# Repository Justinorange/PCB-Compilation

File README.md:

# PCB-Compilation

A collection of custom PCB designs, prototypes, and lab projects built for research and experimentation.

## [Relay Control Board](https://github.com/uf-mil-electrical/NaviGator/tree/3adb6dfac39e3fa88b3697202d415e38e3245c48/Kill%20Board/2026/Relay-Board-PCB/Relay-Board)

A robust relay control and safety management board designed for hardware kill switching, power distribution, and status monitoring.

### Key Features:
- **Relay Outputs:** Features 7 relay outputs with selectable 12V and MCU-level voltage control options, protected by a fuse and TVS diode.
- **Kill & Safety System:** 
  * 6 input signals with individual red status LEDs to monitor when a kill state is active.
  * 2 dedicated inputs for manual override (enables the yellow status indicator; overridden by the red kill state).
  * Active high/low configuration jumpers for flexible input/output logic.
  * Hardware override jumper to unkill the system.
- **Light Tower Status Indicators:** Built using 0803 SMD LEDs for clean labeling and visual feedback:
  * **Enable**
  * **Red:** Kill enabled
  * **Yellow:** Manual enable
  * **Green:** Autonomous / default operation

View the project source and design files on [GitHub](https://github.com/uf-mil-electrical/NaviGator/tree/3adb6dfac39e3fa88b3697202d415e38e3245c48/Kill%20Board/2026/Relay-Board-PCB/Relay-Board).

## [Air Quality Sensor Breakout Boards](https://github.com/uf-mil-electrical/misc_hardware/tree/7a44acb8b002e7d45b233cf23141b061ac4c3471/Sensing/Sensor_Breakouts)

I am building a set of sensor breakout boards that will eventually be combined into a single air quality sensing PCB. These boards are still in progress, and I am finishing the analog sensor boards before moving on to the digital ones.

These breakout boards were made for the Machine Intelligence Laboratory (MIL) and are part of a larger integrated sensing platform. View the breakout designs on [GitHub](https://github.com/uf-mil-electrical/misc_hardware/tree/7a44acb8b002e7d45b233cf23141b061ac4c3471/Sensing/Sensor_Breakouts).

## [STUSB 4500 Controller](https://github.com/Justinorange/STUSB4500-Arduino-Controller)

The STUSB 4500 controller is one of the more complicated PCBs I have made, largely due to the use of USB C protocols and having to solder it by hand.

This board was made for FOCUS Lab last year and represents a more complex design in the collection. View the project source on [GitHub](https://github.com/Justinorange/STUSB4500-Arduino-Controller).

## [Flashlight Project](https://github.com/Justinorange/Flashlight)

This was a quick and fun project to build two flashlights that produce over 20,000 lumens each while keeping the cost as low as possible. The total cost for both was approximately $50. (I also just wanted to make a single sided aluminum PCB).

View the repository and design files on [GitHub](https://github.com/Justinorange/Flashlight).

## Project Summary

This repository highlights a diverse range of custom PCB projects, including modular air quality and hydrogen sensor systems, a comprehensive relay control board with hardware safety features, research-focused USB-C power controllers, and high-output lighting builds.

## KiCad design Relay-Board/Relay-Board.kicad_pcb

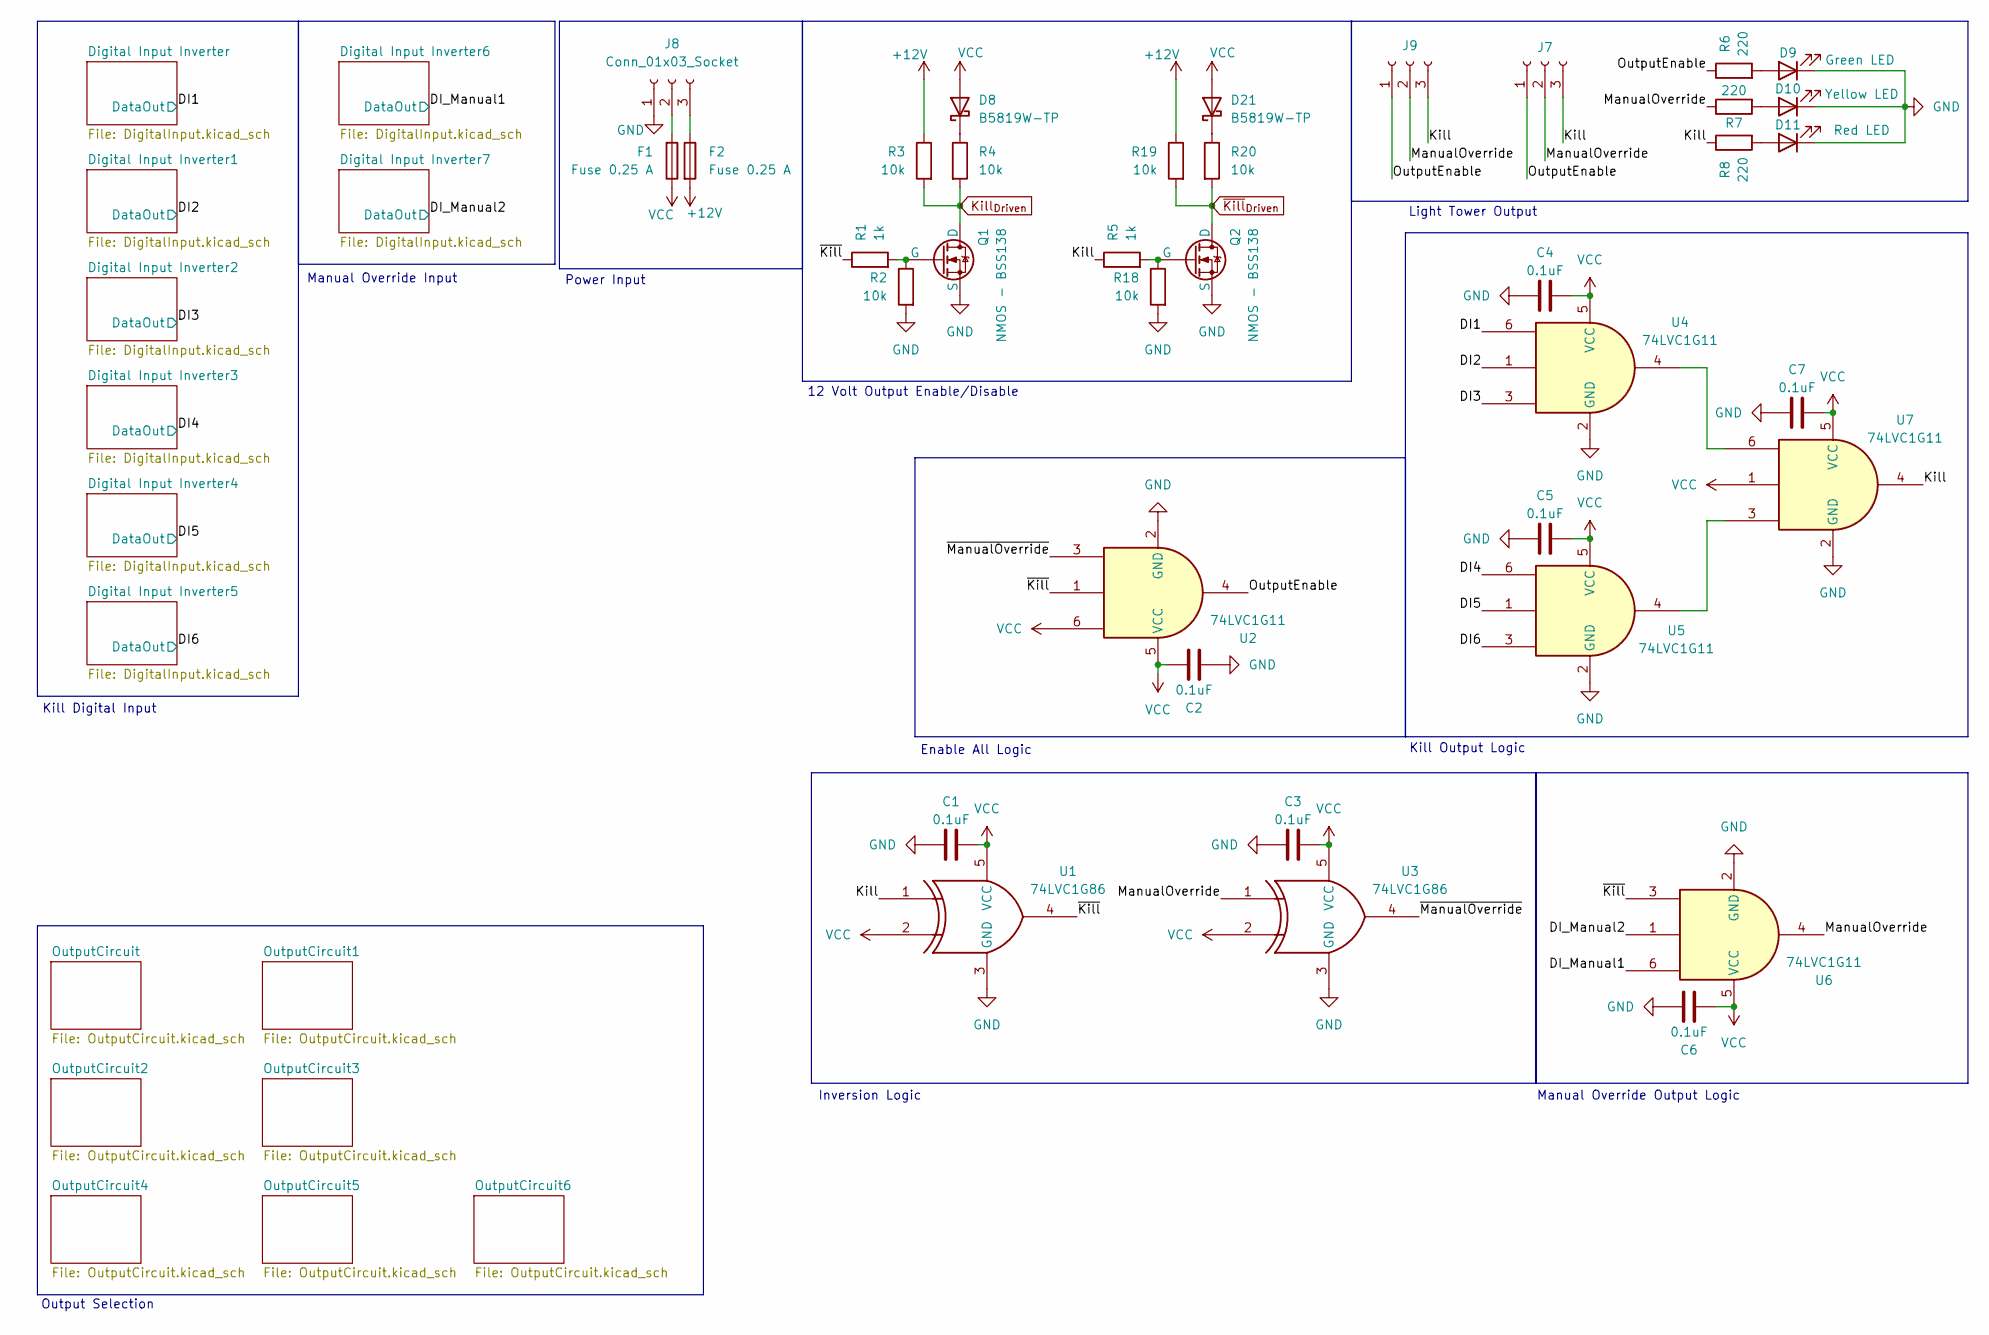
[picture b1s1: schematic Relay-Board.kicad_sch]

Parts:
C1, C2, C3, C4, C5, C6, C7: 0.1uF; C_0603_1608Metric_Pad1.08x0.95mm_HandSolder
D8, D21: B5819W-TP; D_SOD-123
D9: Green LED; LED_0805_2012Metric_Pad1.15x1.40mm_HandSolder
D10: Yellow LED; LED_0805_2012Metric_Pad1.15x1.40mm_HandSolder
D11: Red LED; LED_0805_2012Metric_Pad1.15x1.40mm_HandSolder
F1, F2: Fuse 0.25 A; Fuse_1206_3216Metric_Pad1.42x1.75mm_HandSolder
J7, J8, J9: Conn_01x03_Socket; Molex_Micro-Latch_53253-0370_1x03_P2.00mm_Vertical
Q1, Q2: NMOS - BSS138; SC-59_Handsoldering
R1, R5: 1k; R_0603_1608Metric_Pad0.98x0.95mm_HandSolder
R2, R3, R4, R18, R19, R20: 10k; R_0603_1608Metric_Pad0.98x0.95mm_HandSolder
R6, R7, R8: 220; R_0603_1608Metric_Pad0.98x0.95mm_HandSolder
U1, U3: 74LVC1G86; Texas_R-PDSO-G5_DCK-5
U2, U4, U5, U6, U7: 74LVC1G11; SOT-23-6_Handsoldering

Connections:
+12V: F2.2, R3.1, R19.1; also elsewhere on the board
/DI1: U4.6; also elsewhere on the board
/DI2: U4.1; also elsewhere on the board
/DI3: U4.3; also elsewhere on the board
/DI4: U5.6; also elsewhere on the board
/DI5: U5.1; also elsewhere on the board
/DI6: U5.3; also elsewhere on the board
/DI_Manual1: U6.6; also elsewhere on the board
/DI_Manual2: U6.1; also elsewhere on the board
/Kill: J7.3, J9.3, R5.1, R8.1, U1.1, U7.4
/ManualOverride: J7.2, J9.2, R7.1, U3.1, U6.4
/OutputEnable: J7.1, J9.1, R6.1, U2.4
/~Kill: R1.1, U1.4, U2.1, U6.3
/~ManualOverride: U2.3, U3.4
GND: C1.2, C2.2, C3.2, C4.2, C5.2, C6.2, C7.2, D9.1 (K), D10.1 (K), D11.1 (K), J8.1, Q1.3 (S), Q2.3 (S), R2.2, R18.2, U1.3 (GND), U2.2 (GND), U3.3 (GND), U4.2 (GND), U5.2 (GND), U6.2 (GND), U7.2 (GND); also elsewhere on the board
Kill_{Driven}: Q1.1 (D), R3.2, R4.2; also elsewhere on the board
unnamed: D8.1 (K), R4.1
unnamed: D9.2 (A), R6.2
unnamed: D10.2 (A), R7.2
unnamed: D11.2 (A), R8.2
unnamed: D21.1 (K), R20.1
unnamed: F1.2, J8.2
unnamed: F2.1, J8.3
unnamed: Q1.2 (G), R1.2, R2.1
unnamed: Q2.2 (G), R5.2, R18.1
unnamed: U4.4, U7.6
unnamed: U5.4, U7.3
VCC: C1.1, C2.1, C3.1, C4.1, C5.1, C6.1, C7.1, D8.2 (A), D21.2 (A), F1.1, U1.2, U1.5 (VCC), U2.5 (VCC), U2.6, U3.2, U3.5 (VCC), U4.5 (VCC), U5.5 (VCC), U6.5 (VCC), U7.1, U7.5 (VCC); also elsewhere on the board
~Kill_{Driven}: Q2.1 (D), R19.2, R20.2; also elsewhere on the board

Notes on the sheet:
Kill Digital Input
Output Selection
Power Input
Inversion Logic
Kill Output Logic
Enable All Logic
Manual Override Output Logic
Manual Override Input
Light Tower Output
12 Volt Output Enable/Disable

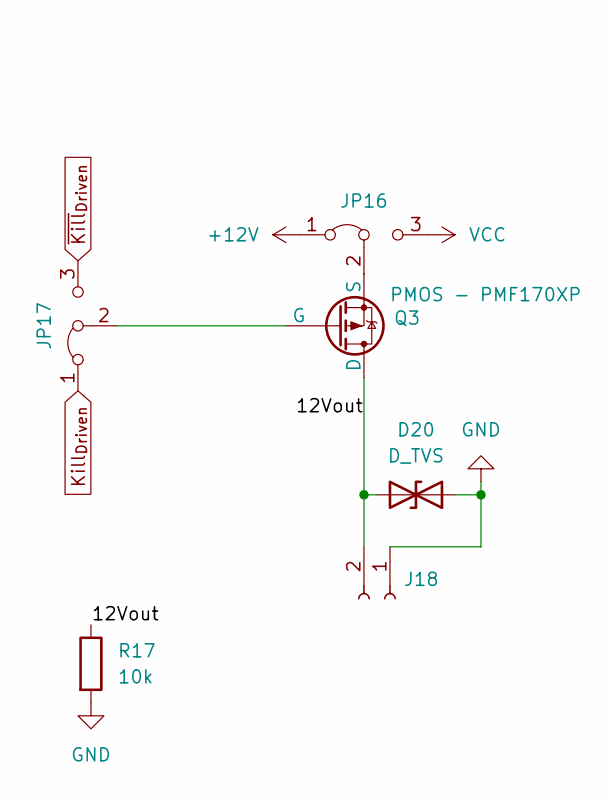
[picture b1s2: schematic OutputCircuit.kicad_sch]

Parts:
D20: D_TVS; D_SMB
J18: Conn_01x02_Socket; Molex_Micro-Latch_53253-0270_1x02_P2.00mm_Vertical
JP16, JP17: Jumper_3_Bridged12; PinHeader_1x03_P2.54mm_Vertical
Q3: PMOS - PMF170XP; SOT-323_SC-70_Handsoldering
R17: 10k; R_0603_1608Metric_Pad0.98x0.95mm_HandSolder

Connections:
+12V: JP16.1 (A); also elsewhere on the board
/OutputCircuit/12Vout: D20.2 (A2), J18.2, Q3.1 (D), R17.1
GND: D20.1 (A1), J18.1, R17.2; also elsewhere on the board
Kill_{Driven}: JP17.1 (A); also elsewhere on the board
unnamed: JP16.2 (C), Q3.3 (S)
unnamed: JP17.2 (C), Q3.2 (G)
VCC: JP16.3 (B); also elsewhere on the board
~Kill_{Driven}: JP17.3 (B); also elsewhere on the board

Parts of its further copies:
D1, D2, D3, D4, D5, D6: D_TVS; D_SMB
J1, J2, J3, J4, J5, J6: Conn_01x02_Socket; Molex_Micro-Latch_53253-0270_1x02_P2.00mm_Vertical
JP1, JP2, JP3, JP4, JP5, JP6, JP7, JP18, JP19, JP20, JP21, JP22: Jumper_3_Bridged12; PinHeader_1x03_P2.54mm_Vertical
Q4, Q5, Q6, Q7, Q8, Q9: PMOS - PMF170XP; SOT-323_SC-70_Handsoldering
R21, R22, R23, R24, R25, R26: 10k; R_0603_1608Metric_Pad0.98x0.95mm_HandSolder

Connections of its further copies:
+12V: JP3.1 (A), JP4.1 (A), JP6.1 (A), JP18.1 (A), JP20.1 (A), JP22.1 (A); also elsewhere on the board
/OutputCircuit1/12Vout: D1.2 (A2), J1.2, Q4.1 (D), R21.1
/OutputCircuit2/12Vout: D2.2 (A2), J2.2, Q5.1 (D), R22.1
/OutputCircuit3/12Vout: D3.2 (A2), J3.2, Q6.1 (D), R23.1
/OutputCircuit4/12Vout: D4.2 (A2), J4.2, Q7.1 (D), R24.1
/OutputCircuit5/12Vout: D5.2 (A2), J5.2, Q8.1 (D), R25.1
/OutputCircuit6/12Vout: D6.2 (A2), J6.2, Q9.1 (D), R26.1
GND: D1.1 (A1), D2.1 (A1), D3.1 (A1), D4.1 (A1), D5.1 (A1), D6.1 (A1), J1.1, J2.1, J3.1, J4.1, J5.1, J6.1, R21.2, R22.2, R23.2, R24.2, R25.2, R26.2; also elsewhere on the board
Kill_{Driven}: JP1.1 (A), JP2.1 (A), JP5.1 (A), JP7.1 (A), JP19.1 (A), JP21.1 (A); also elsewhere on the board
unnamed: JP1.2 (C), Q4.2 (G)
unnamed: JP2.2 (C), Q5.2 (G)
unnamed: JP3.2 (C), Q5.3 (S)
unnamed: JP4.2 (C), Q4.3 (S)
unnamed: JP5.2 (C), Q6.2 (G)
unnamed: JP6.2 (C), Q6.3 (S)
unnamed: JP7.2 (C), Q7.2 (G)
unnamed: JP18.2 (C), Q7.3 (S)
unnamed: JP19.2 (C), Q8.2 (G)
unnamed: JP20.2 (C), Q8.3 (S)
unnamed: JP21.2 (C), Q9.2 (G)
unnamed: JP22.2 (C), Q9.3 (S)
VCC: JP3.3 (B), JP4.3 (B), JP6.3 (B), JP18.3 (B), JP20.3 (B), JP22.3 (B); also elsewhere on the board
~Kill_{Driven}: JP1.3 (B), JP2.3 (B), JP5.3 (B), JP7.3 (B), JP19.3 (B), JP21.3 (B); also elsewhere on the board

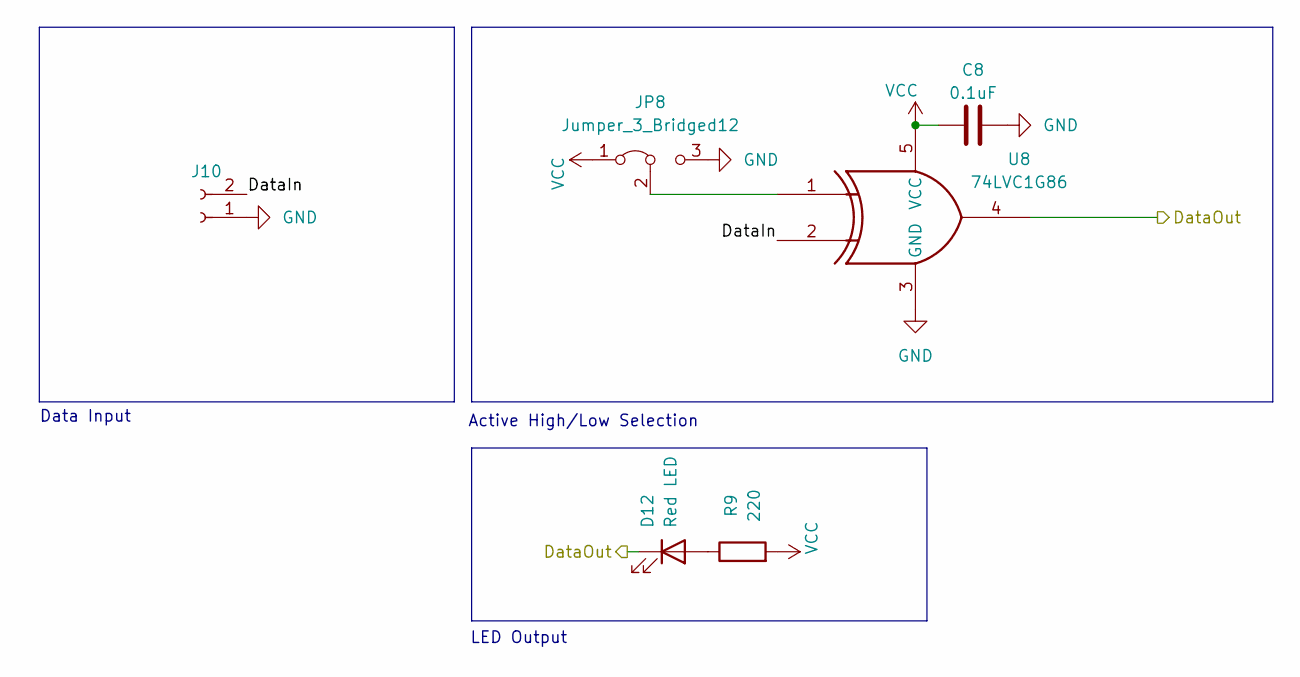
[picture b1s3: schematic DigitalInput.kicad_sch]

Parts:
C8: 0.1uF; C_0603_1608Metric_Pad1.08x0.95mm_HandSolder
D12: Red LED; LED_0805_2012Metric_Pad1.15x1.40mm_HandSolder
J10: Conn_01x02_Socket; Molex_Micro-Latch_53253-0270_1x02_P2.00mm_Vertical
JP8: Jumper_3_Bridged12; PinHeader_1x03_P2.54mm_Vertical
R9: 220; R_0603_1608Metric_Pad0.98x0.95mm_HandSolder
U8: 74LVC1G86; Texas_R-PDSO-G5_DCK-5

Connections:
/DI1: D12.1 (K), U8.4; also elsewhere on the board
/Digital Input Inverter/DataIn: J10.2, U8.2
GND: C8.2, J10.1, JP8.3 (B), U8.3 (GND); also elsewhere on the board
unnamed: D12.2 (A), R9.1
unnamed: JP8.2 (C), U8.1
VCC: C8.1, JP8.1 (A), R9.2, U8.5 (VCC); also elsewhere on the board

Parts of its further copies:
C9, C10, C11, C12, C13, C14, C15: 0.1uF; C_0603_1608Metric_Pad1.08x0.95mm_HandSolder
D13, D14, D15, D16, D17, D18, D19: Red LED; LED_0805_2012Metric_Pad1.15x1.40mm_HandSolder
J11, J12, J13, J14, J15, J16, J17: Conn_01x02_Socket; Molex_Micro-Latch_53253-0270_1x02_P2.00mm_Vertical
JP9, JP10, JP11, JP12, JP13, JP14, JP15: Jumper_3_Bridged12; PinHeader_1x03_P2.54mm_Vertical
R10, R11, R12, R13, R14, R15, R16: 220; R_0603_1608Metric_Pad0.98x0.95mm_HandSolder
U9, U10, U11, U12, U13, U14, U15: 74LVC1G86; Texas_R-PDSO-G5_DCK-5

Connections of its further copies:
/DI2: D13.1 (K), U9.4; also elsewhere on the board
/DI3: D14.1 (K), U10.4; also elsewhere on the board
/DI4: D15.1 (K), U11.4; also elsewhere on the board
/DI5: D16.1 (K), U12.4; also elsewhere on the board
/DI6: D17.1 (K), U13.4; also elsewhere on the board
/DI_Manual1: D18.1 (K), U14.4; also elsewhere on the board
/DI_Manual2: D19.1 (K), U15.4; also elsewhere on the board
/Digital Input Inverter1/DataIn: J11.2, U9.2
/Digital Input Inverter2/DataIn: J12.2, U10.2
/Digital Input Inverter3/DataIn: J13.2, U11.2
/Digital Input Inverter4/DataIn: J14.2, U12.2
/Digital Input Inverter5/DataIn: J15.2, U13.2
/Digital Input Inverter6/DataIn: J16.2, U14.2
/Digital Input Inverter7/DataIn: J17.2, U15.2
GND: C9.2, C10.2, C11.2, C12.2, C13.2, C14.2, C15.2, J11.1, J12.1, J13.1, J14.1, J15.1, J16.1, J17.1, JP9.3 (B), JP10.3 (B), JP11.3 (B), JP12.3 (B), JP13.3 (B), JP14.3 (B), JP15.3 (B), U9.3 (GND), U10.3 (GND), U11.3 (GND), U12.3 (GND), U13.3 (GND), U14.3 (GND), U15.3 (GND); also elsewhere on the board
unnamed: D13.2 (A), R10.1
unnamed: D14.2 (A), R11.1
unnamed: D15.2 (A), R12.1
unnamed: D16.2 (A), R13.1
unnamed: D17.2 (A), R14.1
unnamed: D18.2 (A), R15.1
unnamed: D19.2 (A), R16.1
unnamed: JP9.2 (C), U9.1
unnamed: JP10.2 (C), U10.1
unnamed: JP11.2 (C), U11.1
unnamed: JP12.2 (C), U12.1
unnamed: JP13.2 (C), U13.1
unnamed: JP14.2 (C), U14.1
unnamed: JP15.2 (C), U15.1
VCC: C9.1, C10.1, C11.1, C12.1, C13.1, C14.1, C15.1, JP9.1 (A), JP10.1 (A), JP11.1 (A), JP12.1 (A), JP13.1 (A), JP14.1 (A), JP15.1 (A), R10.2, R11.2, R12.2, R13.2, R14.2, R15.2, R16.2, U9.5 (VCC), U10.5 (VCC), U11.5 (VCC), U12.5 (VCC), U13.5 (VCC), U14.5 (VCC), U15.5 (VCC); also elsewhere on the board

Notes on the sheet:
Active High/Low Selection
LED Output
Data Input

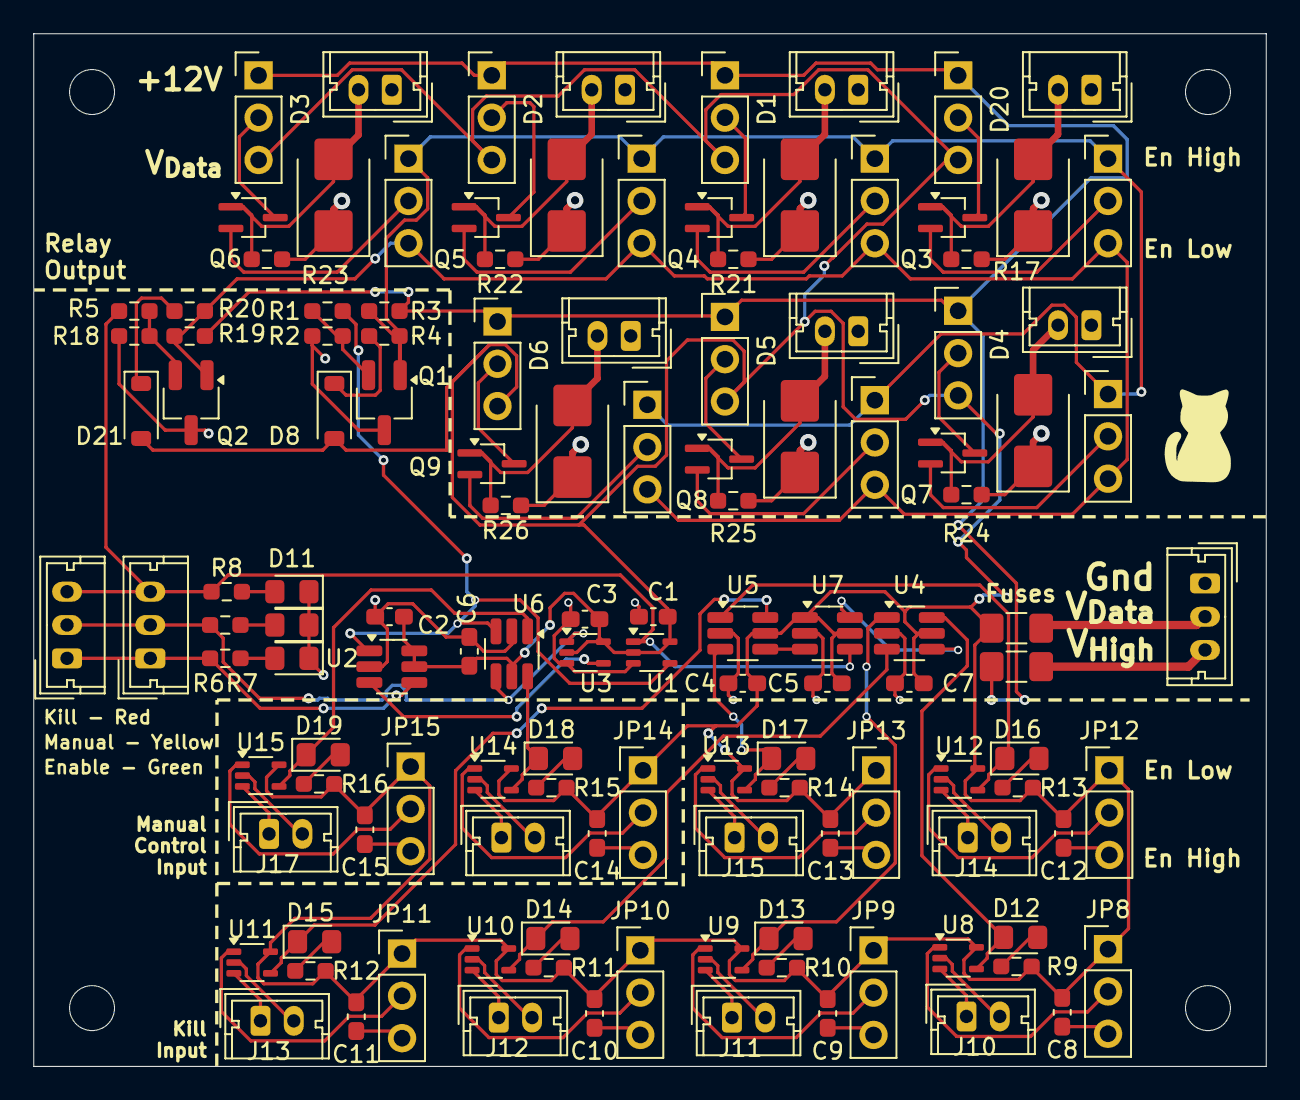
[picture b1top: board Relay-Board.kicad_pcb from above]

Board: 2 copper layers, 74.0 x 62.0 mm, 127 parts (0 on the bottom side), 74 nets.

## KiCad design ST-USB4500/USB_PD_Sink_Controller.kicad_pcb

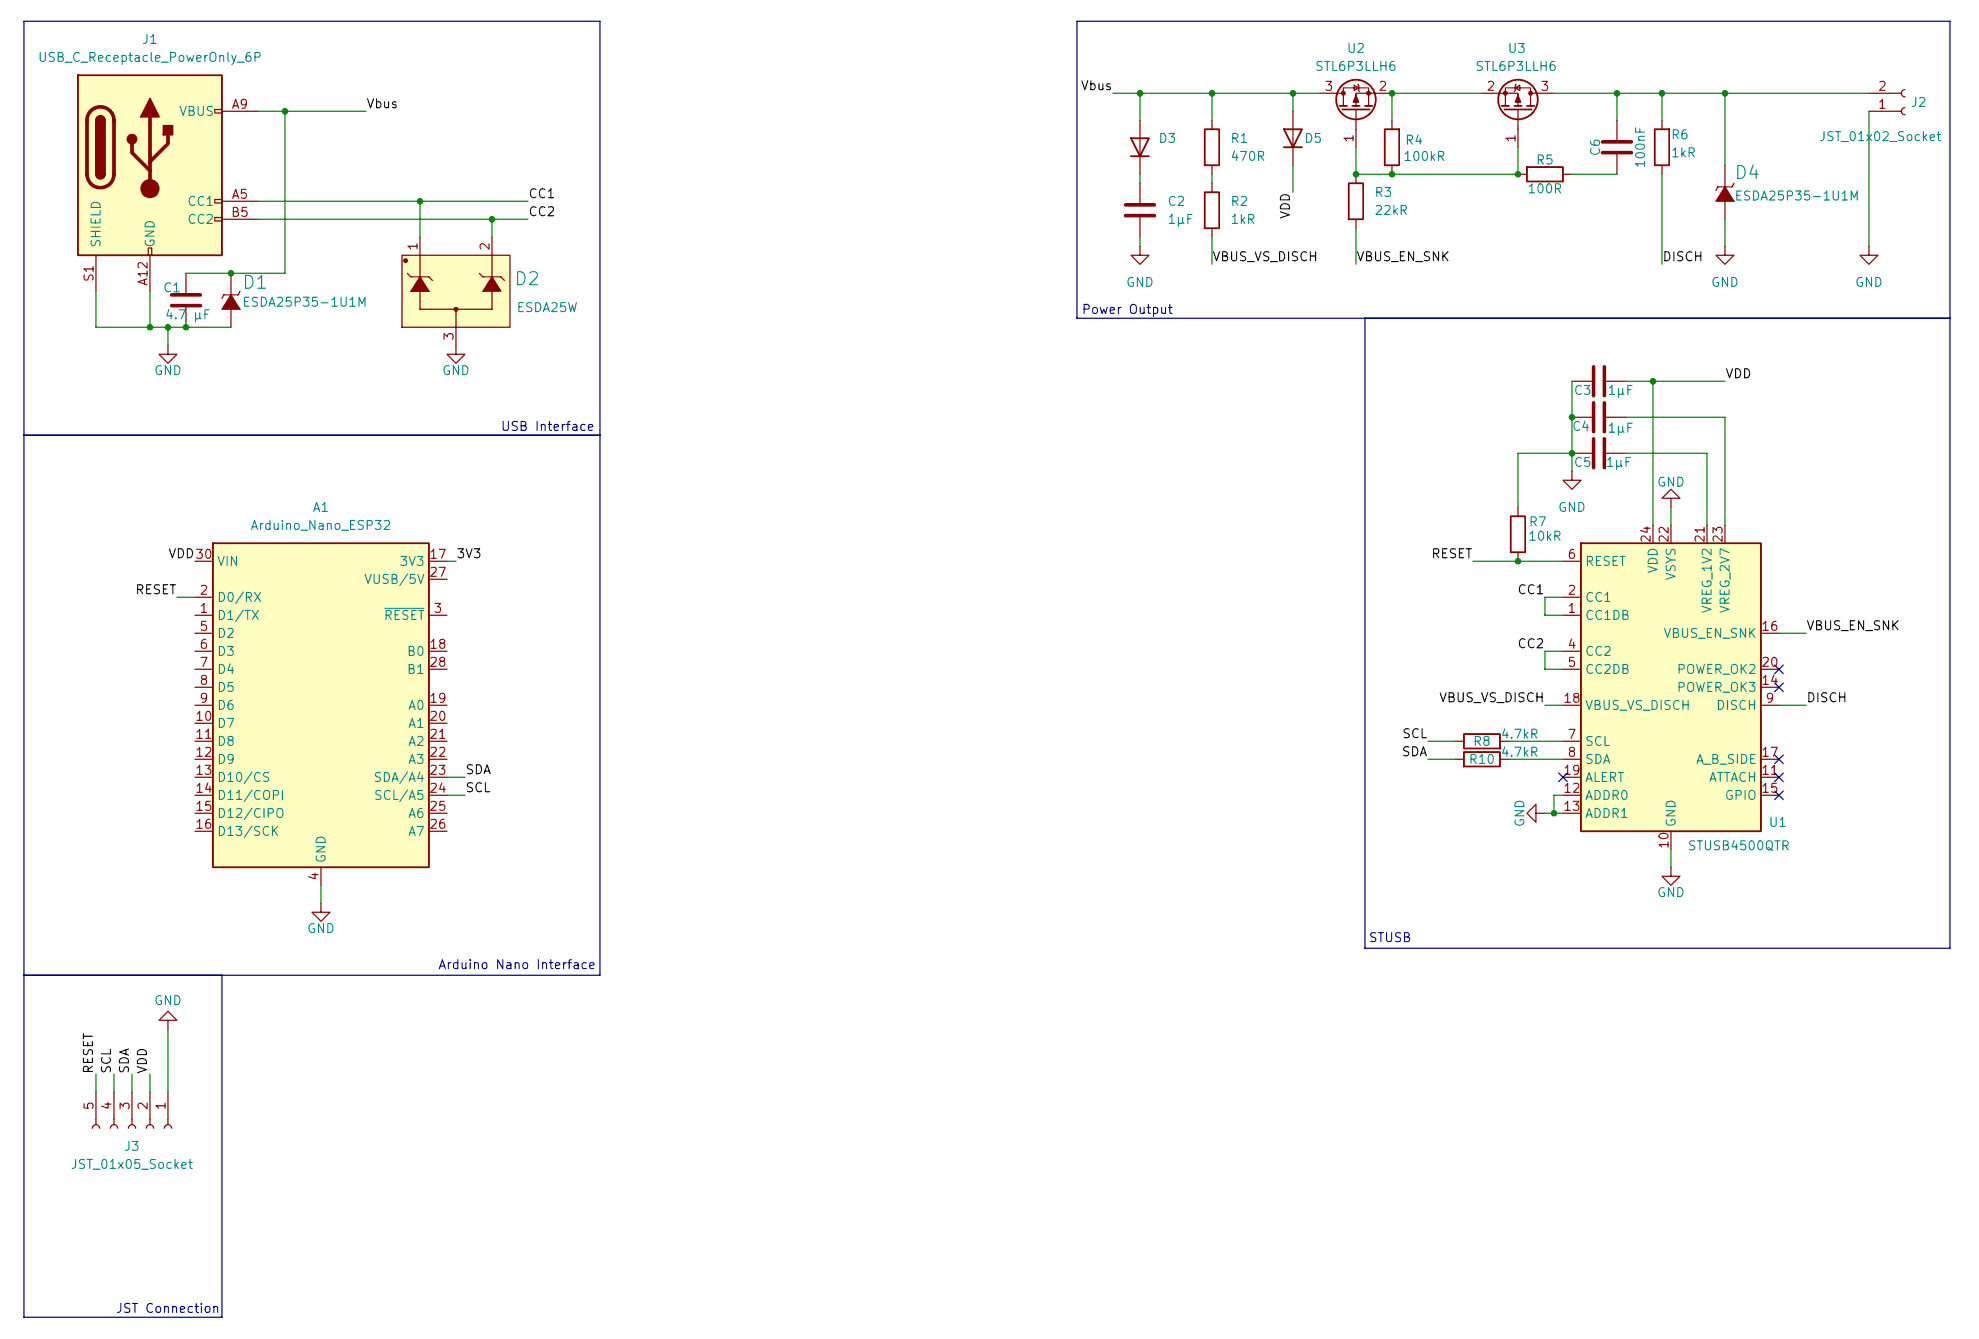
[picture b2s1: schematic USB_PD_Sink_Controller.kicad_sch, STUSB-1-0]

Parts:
A1: Arduino_Nano_ESP32; Arduino_Nano
C1: 4.7 μF; C_0603_1608Metric_Pad1.08x0.95mm_HandSolder
C2, C3, C4, C5: 1μF; C_0603_1608Metric_Pad1.08x0.95mm_HandSolder
C6: 100nF; C_0603_1608Metric_Pad1.08x0.95mm_HandSolder
D1, D4: ESDA25P35-1U1M; ST_1610
D2: ESDA25W; ST_SOT323-3L
D3, D5: D; D_0603_1608Metric_Pad1.05x0.95mm_HandSolder
J1: USB_C_Receptacle_PowerOnly_6P; USB_C_Receptacle_GCT_USB4105-xx-A_16P_TopMnt_Horizontal
J2: JST_01x02_Socket; JST_XH_S2B-XH-A_1x02_P2.50mm_Horizontal
J3: JST_01x05_Socket; JST_XH_S5B-XH-A_1x05_P2.50mm_Horizontal
R1: 470R; R_0603_1608Metric_Pad0.98x0.95mm_HandSolder
R2, R6: 1kR; R_0603_1608Metric_Pad0.98x0.95mm_HandSolder
R3: 22kR; R_0603_1608Metric_Pad0.98x0.95mm_HandSolder
R4: 100kR; R_0603_1608Metric_Pad0.98x0.95mm_HandSolder
R5: 100R; R_0603_1608Metric_Pad0.98x0.95mm_HandSolder
R7: 10kR; R_0603_1608Metric_Pad0.98x0.95mm_HandSolder
R8, R10: 4.7kR; R_0603_1608Metric_Pad0.98x0.95mm_HandSolder
U1: STUSB4500QTR; QFN-24-1EP_4x4mm_P0.5mm_EP2.7x2.7mm
U2, U3: STL6P3LLH6; POWERFLAT_3P3X3P3_STM2

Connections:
/CC1: D2.1, J1.A5 (CC1), U1.1 (CC1DB), U1.2 (CC1)
/CC2: D2.2, J1.B5 (CC2), U1.4 (CC2), U1.5 (CC2DB)
/DISCH: R6.1, U1.9 (DISCH)
/RESET: A1.2 (D0/RX), J3.5, R7.2, U1.6 (RESET)
/SCL: A1.24 (SCL/A5), J3.4, R8.1
/SDA: A1.23 (SDA/A4), J3.3, R10.2
/VBUS_EN_SNK: R3.2, U1.16 (VBUS_EN_SNK)
/VBUS_VS_DISCH: R2.2, U1.18 (VBUS_VS_DISCH)
/VDD: A1.30 (VIN), C3.1, D5.1 (K), J3.2, U1.24 (VDD)
/Vbus: C1.1, D1.1 (K), D3.2 (A), D5.2 (A), J1.A9 (VBUS), J1.B9 (VBUS), R1.1, U2.3 (D)
GND: A1.4 (GND), A1.29 (GND), C1.2, C2.2, C3.2, C4.2, C5.2, D1.2 (A), D2.3, D4.2 (A), J1.A12 (GND), J1.B12 (GND), J1.S1 (SHIELD), J2.1, J3.1, R7.1, U1.10 (GND), U1.12 (ADDR0), U1.13 (ADDR1), U1.22 (VSYS), U1.25 (GND)
unnamed: C6.1, R5.1
unnamed: C2.1, D3.1 (K)
unnamed: C6.2, D4.1 (K), J2.2, R6.2, U3.3 (D)
unnamed: R1.2, R2.1
unnamed: R8.2, U1.7 (SCL)
unnamed: R10.1, U1.8 (SDA)
unnamed: C5.1, U1.21 (VREG_1V2)
unnamed: C4.1, U1.23 (VREG_2V7)
unnamed: R3.1, R4.1, R5.2, U2.1 (G), U3.1 (G)
unnamed: R4.2, U2.2 (S), U3.2 (S)

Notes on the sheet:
STUSB
Arduino Nano Interface
JST Connection
USB Interface
Power Output

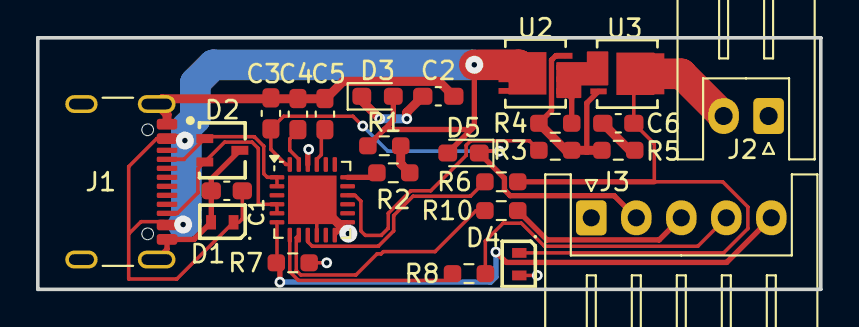
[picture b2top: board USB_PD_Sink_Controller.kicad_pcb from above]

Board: 2 copper layers, 43.5 x 14.0 mm, 26 parts (0 on the bottom side), 21 nets.
